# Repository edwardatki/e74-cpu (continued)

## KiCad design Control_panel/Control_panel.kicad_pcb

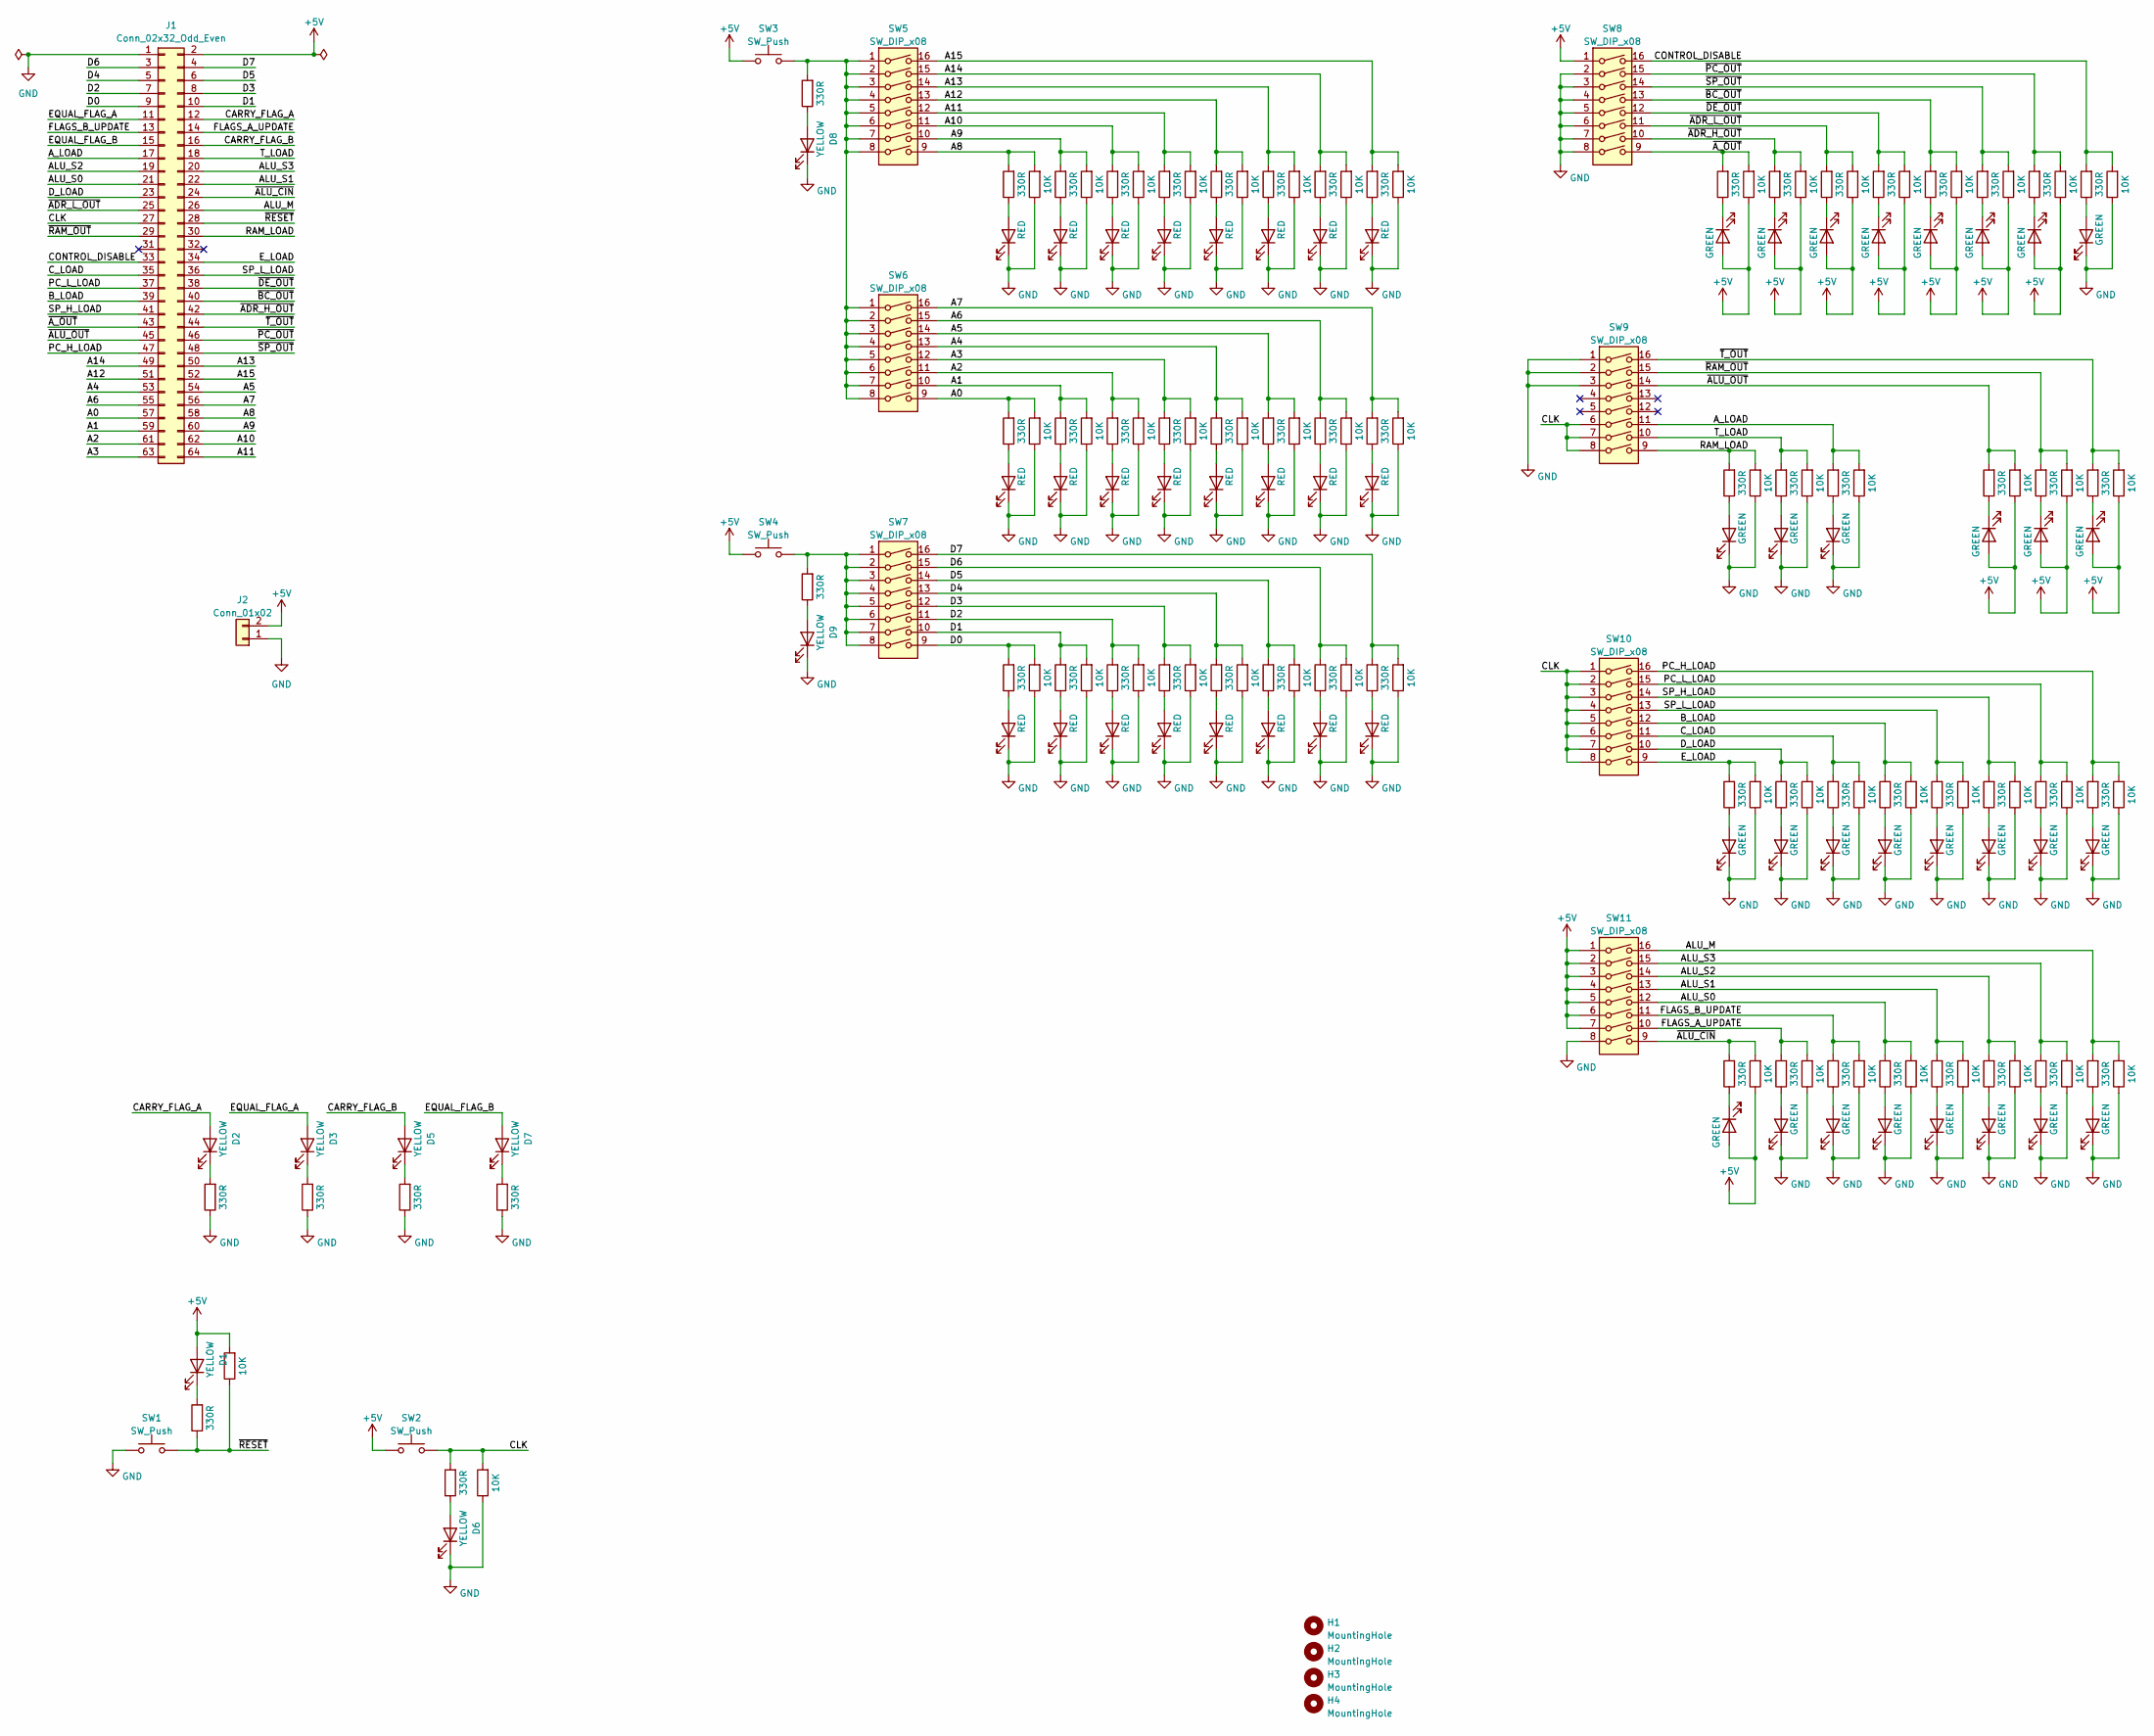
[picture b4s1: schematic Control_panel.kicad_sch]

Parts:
D1, D2, D3, D5, D6, D7, D8, D9: YELLOW; LED_0603_1608Metric_Pad1.05x0.95mm_HandSolder
D10, D11, D12, D13, D14, D15, D16, D17, D18, D19, D20, D21, D22, D23, D24, D25, D26, D27, D28, D29, D30, D31, D32, D33: RED; LED_0603_1608Metric_Pad1.05x0.95mm_HandSolder
D34, D35, D36, D37, D38, D39, D40, D41, D42, D43, D44, D45, D46, D47, D48, D49, D50, D51, D52, D53, D54, D55, D56, D57, D58, D59, D60, D61, D62, D63: GREEN; LED_0603_1608Metric_Pad1.05x0.95mm_HandSolder
H1, H2, H3, H4: MountingHole; MountingHole_3.5mm
J1: Conn_02x32_Odd_Even; IDC-Header_2x32_P2.54mm_Vertical
J2: Conn_01x02; PinSocket_1x02_P2.54mm_Vertical
R1, R2, R4, R6, R7, R9, R10, R11, R12, R13, R14, R18, R19, R20, R24, R25, R26, R30, R31, R32, R36, R37, R38, R42, R43, R44, R48, R49, R50, R54, R55, R56, R60, R61, R62, R63, R68, R69, R70, R71, R76, R77, R78, R79, R84, R85, R86, R90, R91, R92, R96, R97, R98, R99, R104, R105, R106, R107, R112, R113, R114, R115: 330R; R_0603_1608Metric_Pad0.98x0.95mm_HandSolder
R3, R8, R15, R16, R17, R21, R22, R23, R27, R28, R29, R33, R34, R35, R39, R40, R41, R45, R46, R47, R51, R52, R53, R57, R58, R59, R64, R65, R66, R67, R72, R73, R74, R75, R80, R81, R82, R83, R87, R88, R89, R93, R94, R95, R100, R101, R102, R103, R108, R109, R110, R111, R116, R117, R118, R119: 10K; R_0603_1608Metric_Pad0.98x0.95mm_HandSolder
SW1, SW2, SW3, SW4: SW_Push; SW_PUSH_6mm
SW5, SW6, SW7, SW8, SW9, SW10, SW11: SW_DIP_x08; SW_DIP_SPSTx08_Slide_9.78x22.5mm_W7.62mm_P2.54mm

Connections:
+5V: D1.2 (A), D34.2 (A), D37.2 (A), D38.2 (A), D42.2 (A), D46.2 (A), D49.2 (A), D52.2 (A), D53.2 (A), D56.2 (A), D57.2 (A), D61.2 (A), J1.2, J2.2, R3.2, R64.1, R67.1, R72.1, R80.1, R87.1, R93.1, R100.1, R101.1, R108.1, R109.1, R117.1, SW2.1, SW3.1, SW4.1, SW8.1, SW11.1, SW11.2, SW11.3, SW11.4, SW11.5, SW11.6, SW11.7
/A0: J1.57, R13.2, R16.2, SW6.9
/A1: J1.59, R19.2, R22.2, SW6.10
/A2: J1.61, R25.2, R28.2, SW6.11
/A3: J1.63, R31.2, R34.2, SW6.12
/A4: J1.53, R37.2, R40.2, SW6.13
/A5: J1.54, R43.2, R46.2, SW6.14
/A6: J1.55, R49.2, R52.2, SW6.15
/A7: J1.56, R55.2, R58.2, SW6.16
/A8: J1.58, R12.2, R15.2, SW5.9
/A9: J1.60, R18.2, R21.2, SW5.10
/A10: J1.62, R24.2, R27.2, SW5.11
/A11: J1.64, R30.2, R33.2, SW5.12
/A12: J1.51, R36.2, R39.2, SW5.13
/A13: J1.50, R42.2, R45.2, SW5.14
/A14: J1.49, R48.2, R51.2, SW5.15
/A15: J1.52, R54.2, R57.2, SW5.16
/ALU_M: J1.26, R115.2, R119.2, SW11.16
/ALU_S0: J1.21, R86.2, R89.2, SW11.12
/ALU_S1: J1.22, R92.2, R95.2, SW11.13
/ALU_S2: J1.19, R99.2, R103.2, SW11.14
/ALU_S3: J1.20, R107.2, R111.2, SW11.15
/A_LOAD: J1.17, R77.2, R81.2, SW9.11
/B_LOAD: J1.39, R85.2, R88.2, SW10.12
/CARRY_FLAG_A: D2.2 (A), J1.12
/CARRY_FLAG_B: D5.2 (A), J1.16
/CLK: J1.27, R7.2, R8.2, SW2.2, SW9.6, SW9.7, SW9.8, SW10.1, SW10.2, SW10.3, SW10.4, SW10.5, SW10.6, SW10.7, SW10.8
/CONTROL_DISABLE: J1.33, R112.2, R116.2, SW8.16
/C_LOAD: J1.35, R78.2, R82.2, SW10.11
/D0: J1.9, R14.2, R17.2, SW7.9
/D1: J1.10, R20.2, R23.2, SW7.10
/D2: J1.7, R26.2, R29.2, SW7.11
/D3: J1.8, R32.2, R35.2, SW7.12
/D4: J1.5, R38.2, R41.2, SW7.13
/D5: J1.6, R44.2, R47.2, SW7.14
/D6: J1.3, R50.2, R53.2, SW7.15
/D7: J1.4, R56.2, R59.2, SW7.16
/D_LOAD: J1.23, R70.2, R74.2, SW10.10
/EQUAL_FLAG_A: D3.2 (A), J1.11
/EQUAL_FLAG_B: D7.2 (A), J1.15
/E_LOAD: J1.34, R62.2, R66.2, SW10.9
/FLAGS_A_UPDATE: J1.14, R71.2, R75.2, SW11.10
/FLAGS_B_UPDATE: J1.13, R79.2, R83.2, SW11.11
/PC_H_LOAD: J1.47, R114.2, R118.2, SW10.16
/PC_L_LOAD: J1.37, R106.2, R110.2, SW10.15
/RAM_LOAD: J1.30, R61.2, R65.2, SW9.9
/SP_H_LOAD: J1.41, R98.2, R102.2, SW10.14
/SP_L_LOAD: J1.36, R91.2, R94.2, SW10.13
/T_LOAD: J1.18, R69.2, R73.2, SW9.10
/~ADR_H_OUT: J1.42, R68.2, R72.2, SW8.10
/~ADR_L_OUT: J1.25, R76.2, R80.2, SW8.11
/~ALU_CIN: J1.24, R63.2, R67.2, SW11.9
/~ALU_OUT: J1.45, R97.2, R101.2, SW9.14
/~A_OUT: J1.43, R60.2, R64.2, SW8.9
/~BC_OUT: J1.40, R90.2, R93.2, SW8.13
/~DE_OUT: J1.38, R84.2, R87.2, SW8.12
/~PC_OUT: J1.46, R104.2, R108.2, SW8.15
/~RAM_OUT: J1.29, R105.2, R109.2, SW9.15
/~RESET: J1.28, R1.1, R3.1, SW1.2
/~SP_OUT: J1.48, R96.2, R100.2, SW8.14
/~T_OUT: J1.44, R113.2, R117.2, SW9.16
GND: D6.1 (K), D8.1 (K), D9.1 (K), D10.1 (K), D11.1 (K), D12.1 (K), D13.1 (K), D14.1 (K), D15.1 (K), D16.1 (K), D17.1 (K), D18.1 (K), D19.1 (K), D20.1 (K), D21.1 (K), D22.1 (K), D23.1 (K), D24.1 (K), D25.1 (K), D26.1 (K), D27.1 (K), D28.1 (K), D29.1 (K), D30.1 (K), D31.1 (K), D32.1 (K), D33.1 (K), D35.1 (K), D36.1 (K), D39.1 (K), D40.1 (K), D41.1 (K), D43.1 (K), D44.1 (K), D45.1 (K), D47.1 (K), D48.1 (K), D50.1 (K), D51.1 (K), D54.1 (K), D55.1 (K), D58.1 (K), D59.1 (K), D60.1 (K), D62.1 (K), D63.1 (K), J1.1, J2.1, R2.1, R4.1, R6.1, R8.1, R9.1, R15.1, R16.1, R17.1, R21.1, R22.1, R23.1, R27.1, R28.1, R29.1, R33.1, R34.1, R35.1, R39.1, R40.1, R41.1, R45.1, R46.1, R47.1, R51.1, R52.1, R53.1, R57.1, R58.1, R59.1, R65.1, R66.1, R73.1, R74.1, R75.1, R81.1, R82.1, R83.1, R88.1, R89.1, R94.1, R95.1, R102.1, R103.1, R110.1, R111.1, R116.1, R118.1, R119.1, SW1.1, SW8.2, SW8.3, SW8.4, SW8.5, SW8.6, SW8.7, SW8.8, SW9.1, SW9.2, SW9.3, SW11.8
unnamed: D1.1 (K), R1.2
unnamed: D2.1 (K), R2.2
unnamed: D3.1 (K), R4.2
unnamed: D5.1 (K), R6.2
unnamed: D6.2 (A), R7.1
unnamed: D7.1 (K), R9.2
unnamed: D8.2 (A), R10.1
unnamed: D9.2 (A), R11.1
unnamed: D10.2 (A), R12.1
unnamed: D11.2 (A), R13.1
unnamed: D12.2 (A), R14.1
unnamed: D13.2 (A), R18.1
unnamed: D14.2 (A), R19.1
unnamed: D15.2 (A), R20.1
unnamed: D16.2 (A), R24.1
unnamed: D17.2 (A), R25.1
unnamed: D18.2 (A), R26.1
unnamed: D19.2 (A), R30.1
unnamed: D20.2 (A), R31.1
unnamed: D21.2 (A), R32.1
unnamed: D22.2 (A), R36.1
unnamed: D23.2 (A), R37.1
unnamed: D24.2 (A), R38.1
unnamed: D25.2 (A), R42.1
unnamed: D26.2 (A), R43.1
unnamed: D27.2 (A), R44.1
unnamed: D28.2 (A), R48.1
unnamed: D29.2 (A), R49.1
unnamed: D30.2 (A), R50.1
unnamed: D31.2 (A), R54.1
unnamed: D32.2 (A), R55.1
unnamed: D33.2 (A), R56.1
unnamed: D34.1 (K), R60.1
unnamed: D35.2 (A), R61.1
unnamed: D36.2 (A), R62.1
unnamed: D37.1 (K), R63.1
unnamed: D38.1 (K), R68.1
unnamed: D39.2 (A), R69.1
unnamed: D40.2 (A), R70.1
unnamed: D41.2 (A), R71.1
unnamed: D42.1 (K), R76.1
unnamed: D43.2 (A), R77.1
unnamed: D44.2 (A), R78.1
unnamed: D45.2 (A), R79.1
unnamed: D46.1 (K), R84.1
unnamed: D47.2 (A), R85.1
unnamed: D48.2 (A), R86.1
unnamed: D49.1 (K), R90.1
unnamed: D50.2 (A), R91.1
unnamed: D51.2 (A), R92.1
unnamed: D52.1 (K), R96.1
unnamed: D53.1 (K), R97.1
unnamed: D54.2 (A), R98.1
unnamed: D55.2 (A), R99.1
unnamed: D56.1 (K), R104.1
unnamed: D57.1 (K), R105.1
unnamed: D58.2 (A), R106.1
unnamed: D59.2 (A), R107.1
unnamed: D60.2 (A), R112.1
unnamed: D61.1 (K), R113.1
unnamed: D62.2 (A), R114.1
unnamed: D63.2 (A), R115.1
unnamed: R10.2, SW3.2, SW5.1, SW5.2, SW5.3, SW5.4, SW5.5, SW5.6, SW5.7, SW5.8, SW6.1, SW6.2, SW6.3, SW6.4, SW6.5, SW6.6, SW6.7, SW6.8
unnamed: R11.2, SW4.2, SW7.1, SW7.2, SW7.3, SW7.4, SW7.5, SW7.6, SW7.7, SW7.8

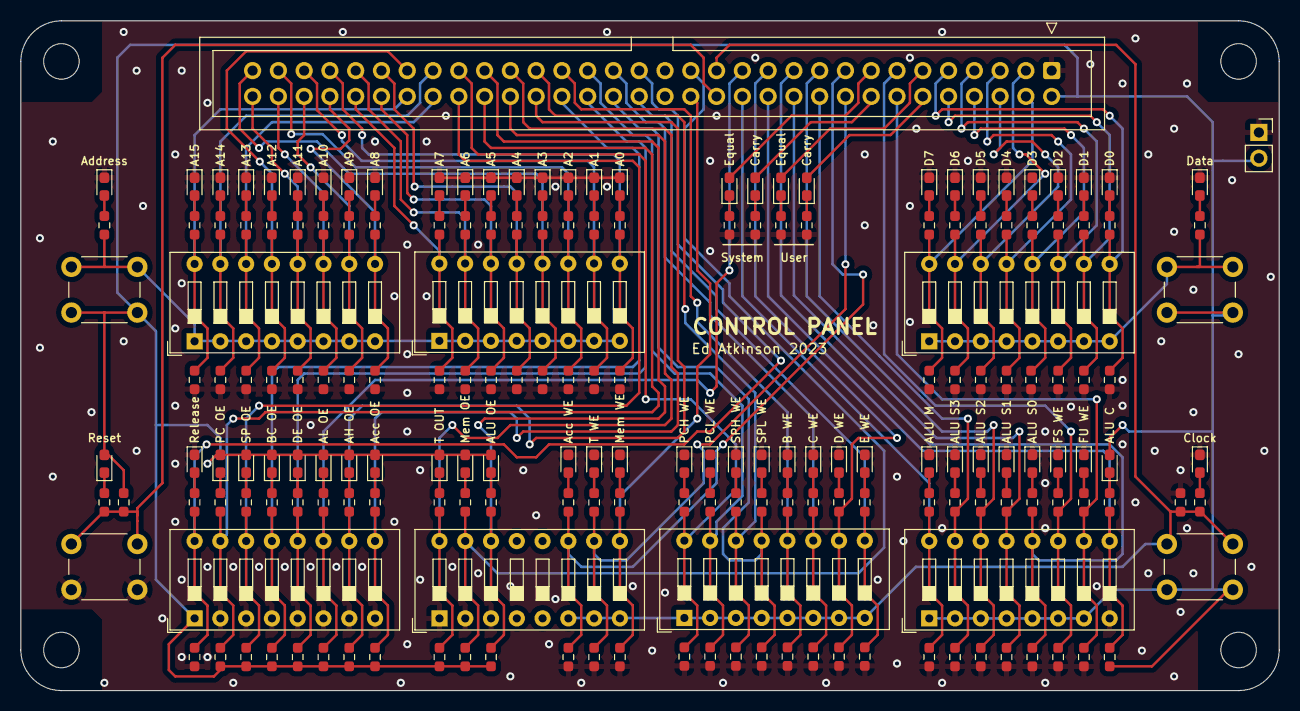
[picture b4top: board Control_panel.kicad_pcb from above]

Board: 2 copper layers, 124.0 x 66.0 mm, 197 parts (0 on the bottom side), 126 nets.

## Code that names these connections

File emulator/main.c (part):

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#define ALU_MODE 0x00020000
#define nAL_OUT 0x00040000
#define ALU_CARRY 0x00080000
#define ALU_S0 0x00100000
#define ALU_S1 0x00200000
#define ALU_S2 0x00400000
#define ALU_S3 0x00800000

#define A_WRITE 0x01000000
#define T_WRITE 0x02000000
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uint8_t user_carry_flag = 0;
uint8_t user_equal_flag = 0;
uint8_t sys_carry_flag = 0;
uint8_t interrupt_flag = 0;
uint8_t interrupt_enable = 0;

uint8_t instr_reg = 0;
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        uint32_t control_word = microcode[control_address];

        if (control_word & IE_TOGGLE) interrupt_enable = !interrupt_enable;
        if (!interrupt_enable) interrupt_flag = 0;

        // Determine value on address bus
        uint16_t address_bus = 0;
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            micro_counter = 0;

            if (interrupt_enable && (waiting_char != 0)) {
                interrupt_flag = 1;
            }
        }

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
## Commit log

2023-06-12 asdf
2023-08-22 qwer
2023-08-22 Register board schematic
2023-08-23 Register board
2023-08-23 Control panel schematic
2023-08-25 Register board and Control panel ordered
2023-08-31 More instructions implemented
2023-09-02 Started on microcode control board
2023-09-02 Fix address line labelling error
2023-09-03 Control board progress
2023-09-04 No progress but more thoughts
2023-09-05 Clock generator done... probably
2023-09-08 Control board schematic done?
2023-09-09 Control board ready for routing
2023-09-10 Control board and connector bridge ready for ordering
2023-09-10 Memory board
2023-09-11 Update logisim to match actual boards
2023-09-11 Interrupts!
2023-09-12 Fix broken logisim 74181
2023-09-12 Flags can be saved to stack
2023-09-13 Simple monitor working
2023-09-13 Some demo programs
2023-09-14 Fast primes demo
2023-09-14 Emulator
2023-09-15 Game of life demo
2023-09-17 Real hardware almost ready for full test
2023-09-18 Added a simple disassembler
2023-09-19 Lowercase, whitespace skipping, optional end address argument for disassemble
2023-09-20 Actual hardware printed its first characters!
2023-09-21 Variable clock frequency
2023-09-22 More microcode wooooo!
2023-09-23 Can dump memory within range, slightly busted though
2023-09-24 Some clean-up of the demo programs
2023-09-27 Emulator initializes RAM with random data
2023-10-02 Variable clock speed, real hardware becomes unstable above ~ 2KHz
2023-10-04 Instructions for dereferencing pointers easier
2023-10-05 Running faster but serial input somewhat unreliable
2023-10-06 I was slightly optimistic but now stable at 10kHz :)
2023-10-09 Tool for converting a program to monitor commands
2023-10-31 Faster upload protocol
2023-11-02 Changes to support new upload protocol
2024-01-04 Update emulator for use in compiler testing
2024-01-05 Move hardware to new folder and delete outdated designs
2024-01-12 Fix and update logisim simulation
2024-01-12 Experiment with some 16-bit arithmetic instructions
